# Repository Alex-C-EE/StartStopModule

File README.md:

# StartStopModule
A repo containing original and custom start stop modules for robo sumo and their firmware. Manufacturing files generated.

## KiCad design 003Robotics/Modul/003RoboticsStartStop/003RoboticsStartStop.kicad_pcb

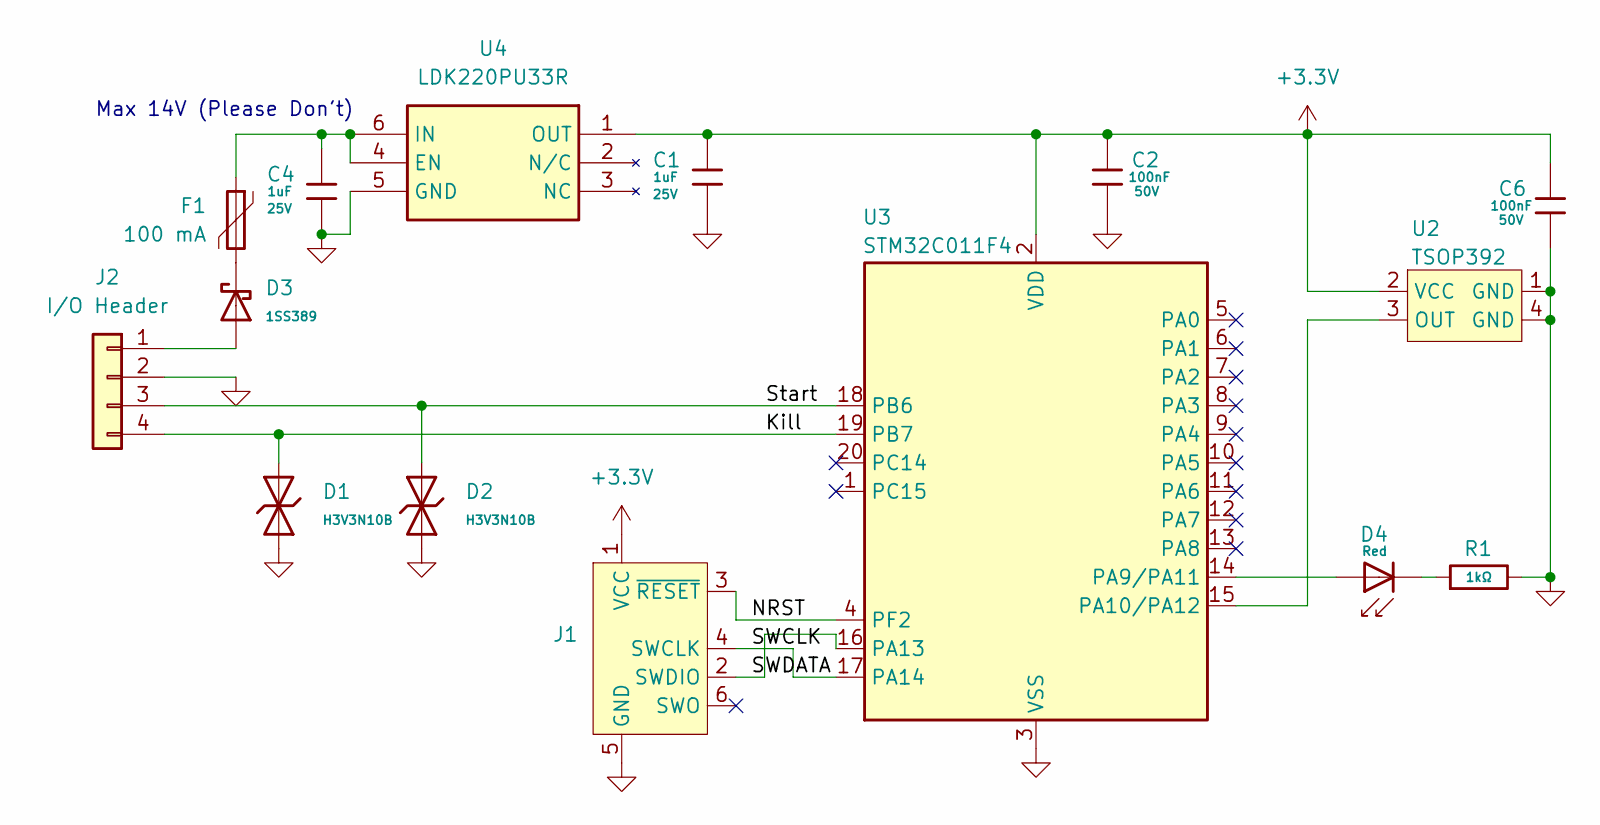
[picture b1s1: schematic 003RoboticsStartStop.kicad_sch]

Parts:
C1, C4: 1uF; C_0402; Voltage Rated 25V; Tolerance ±10%; Part CL05A105KA5NQNC; LCSC C52923
C2, C6: 100nF; C_0402; Voltage Rated 50V; Tolerance ±10%; Part CL05B104KB54PNC; LCSC C307331
D1, D2: H3V3N10B; D_DFN1006-2L; Part H3V3N10B; LCSC C20617909
D3: 1SS389; D_SOD-523; Part 1SS389; LCSC C22466369
D4: Red; D_0603; Part KT-0603R; LCSC C2286
F1: 100 mA; Fuse_0603_1608Metric
J1: Conn_ARM_SWD_TagConnect_TC2030-NL; Tag-Connect_TC2030-IDC-NL_2x03_P1.27mm_Vertical
J2: I/O Header; PinHeader_1x04_P2.54mm_Vertical
R1: 1kΩ; R_0402; Overload Voltage (Max) 50V; Tolerance ±1%; Part 0402WGF1001TCE; LCSC C11702
U2: TSOP392; TVCastSMD4
U3: STM32C011F4; ST_UFQFPN-20_3x3mm_P0.5mm
U4: LDK220PU33R; Mouser Part Number 511-LDK220PU33R

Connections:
+3.3V: C1.1, C2.1, C6.1, J1.1 (VCC), U2.2 (VCC), U3.2 (VDD), U4.1 (OUT)
/Kill: D1.2, J2.4, U3.19 (PB7)
/NRST: J1.3 (~RESET), U3.4 (PF2)
/SWCLK: J1.4 (SWCLK), U3.17 (PA14)
/SWDATA: J1.2 (SWDIO), U3.16 (PA13)
/Start: D2.2, J2.3, U3.18 (PB6)
GND: C1.2, C2.2, C4.2, C6.2, D1.1, D2.1, J1.5 (GND), J2.2, R1.2, U2.1 (GND), U2.4 (GND), U3.3 (VSS), U4.5 (GND)
unnamed: D3.1, F1.2
unnamed: D4.1, R1.1
unnamed: D3.2, J2.1
unnamed: U2.3 (OUT), U3.15 (PA10/PA12)
unnamed: D4.2, U3.14 (PA9/PA11)
unnamed: C4.1, F1.1, U4.4 (EN), U4.6 (IN)

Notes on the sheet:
Max 14V (Please Don't)

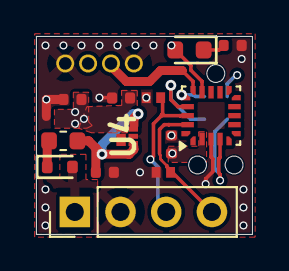
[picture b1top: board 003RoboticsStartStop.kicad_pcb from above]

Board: 4 copper layers, 12.0 x 11.0 mm, 15 parts (1 on the bottom side), 13 nets.

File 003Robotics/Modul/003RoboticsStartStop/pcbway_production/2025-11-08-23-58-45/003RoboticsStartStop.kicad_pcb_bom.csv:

Designator,Quantity,Value,Footprint,Package,MPN,DNP,Mount_Type,Description,LCSC,Stock,Price,Process,Minimum Qty,Attrition Qty,Class,Category,Manufacturer,Part,Voltage Rated,Tolerance,Capacitance,Temperature Coefficient,Resistance,Power(Watts),Type,Overload Voltage (Max),Operating Temperature Range,Height,Mouser Part Number,Mouser Price/Stock,Manufacturer_Name
"C1, C4",2,1uF,C_0402,,,,smt,25V 1uF X5R ±10% 0402 Multilayer Ceramic Capacitors MLCC - SMD/SMT ROHS,C52923,7796525,0.006USD,SMT,20,10,Basic Component,"Capacitors,Multilayer Ceramic Capacitors MLCC - SMD/SMT",Samsung Electro-Mechanics,CL05A105KA5NQNC,25V,±10%,1uF,X5R,,,,,,,,,
"C2, C6",2,100nF,C_0402,,,,smt,50V 100nF X7R ±10% 0402 Multilayer Ceramic Capacitors MLCC - SMD/SMT ROHS,C307331,4519544,0.008USD,SMT,20,10,Basic Component,"Capacitors,Multilayer Ceramic Capacitors MLCC - SMD/SMT",Samsung Electro-Mechanics,CL05B104KB54PNC,50V,±10%,100nF,X7R,,,,,,,,,
"D1, D2",2,H3V3N10B,D_DFN1006-2L,,,,smt,8A 10V 80W 6V Bidirectional 3.3V DFN1006-2L ESD and Surge Protection (TVS/ESD) ROHS,C20617909,5860,0.016USD,SMT,20,10,Preferred Component,"TVS/Fuse/Board Level Protection,Electrostatic And Surge Protection (TVS/ESD)",hongjiacheng,H3V3N10B,,,,,,,,,,,,,
D3,1,1SS389,D_SOD-523,,,,smt,10V Independent Type 500mV@100mA 100mA SOD-523 Schottky Diodes ROHS,C22466369,4454,0.016USD,SMT,20,6,Preferred Component,"Diodes,Schottky Diodes",hongjiacheng,1SS389,,,,,,,,,,,,,
D4,1,Red,D_0603,,,,smt,-40°C~+85°C Red 0603 LED Indication - Discrete ROHS,C2286,2875790,0.009USD,SMT,20,6,Basic Component,"Optocouplers & LEDs & Infrared,Light Emitting Diodes (LED)",Hubei KENTO Elec,KT-0603R,,,,,,,,,,,,,
F1,1,100 mA,Fuse_0603_1608Metric,,,,smt,"Resettable fuse, polymeric positive temperature coefficient",,,,,,,,,,,,,,,,,,,,,,,
J2,1,I/O Header,PinHeader_1x04_P2.54mm_Vertical,,,,tht,"Generic connector, single row, 01x04, script generated (kicad-library-utils/schlib/autogen/connector/)",,,,,,,,,,,,,,,,,,,,,,,
R1,1,1kΩ,R_0402,,,,tht,62.5mW Thick Film Resistors 50V ±100ppm/°C ±1% 1kΩ 0402 Chip Resistor - Surface Mount ROHS,C11702,6792566,0.004USD,SMT,20,10,Basic Component,"Resistors,Chip Resistor - Surface Mount",UNI-ROYAL(Uniroyal Elec),0402WGF1001TCE,,±1%,,±100ppm/°C,1kΩ,62.5mW,Thick Film Resistors,50V,-55°C~+155°C,,,,
U2,1,TSOP392,TVCastSMD4,,,,smt,,,,,,,,,,,,,,,,,,,,,,,,
U3,1,STM32C011F4,ST_UFQFPN-20_3x3mm_P0.5mm,,,,smt,"STMicroelectronics Arm Cortex-M0+ MCU, 16KB flash, 6KB RAM, 48 MHz, 2.0-3.6V, 18 GPIO, UFQFPN20",,,,,,,,,,,,,,,,,,,,,,,
U4,1,LDK220PU33R,LDK220PU33R,,LDK220PU33R,,smt,LDO Voltage Regulators 200 mA low quiescent current and low noise LDO,,,,,,,,,,,,,,,,,,,,0.5,511-LDK220PU33R,https://www.mouser.co.uk/ProductDetail/STMicroelectronics/LD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,STMicroelectronics

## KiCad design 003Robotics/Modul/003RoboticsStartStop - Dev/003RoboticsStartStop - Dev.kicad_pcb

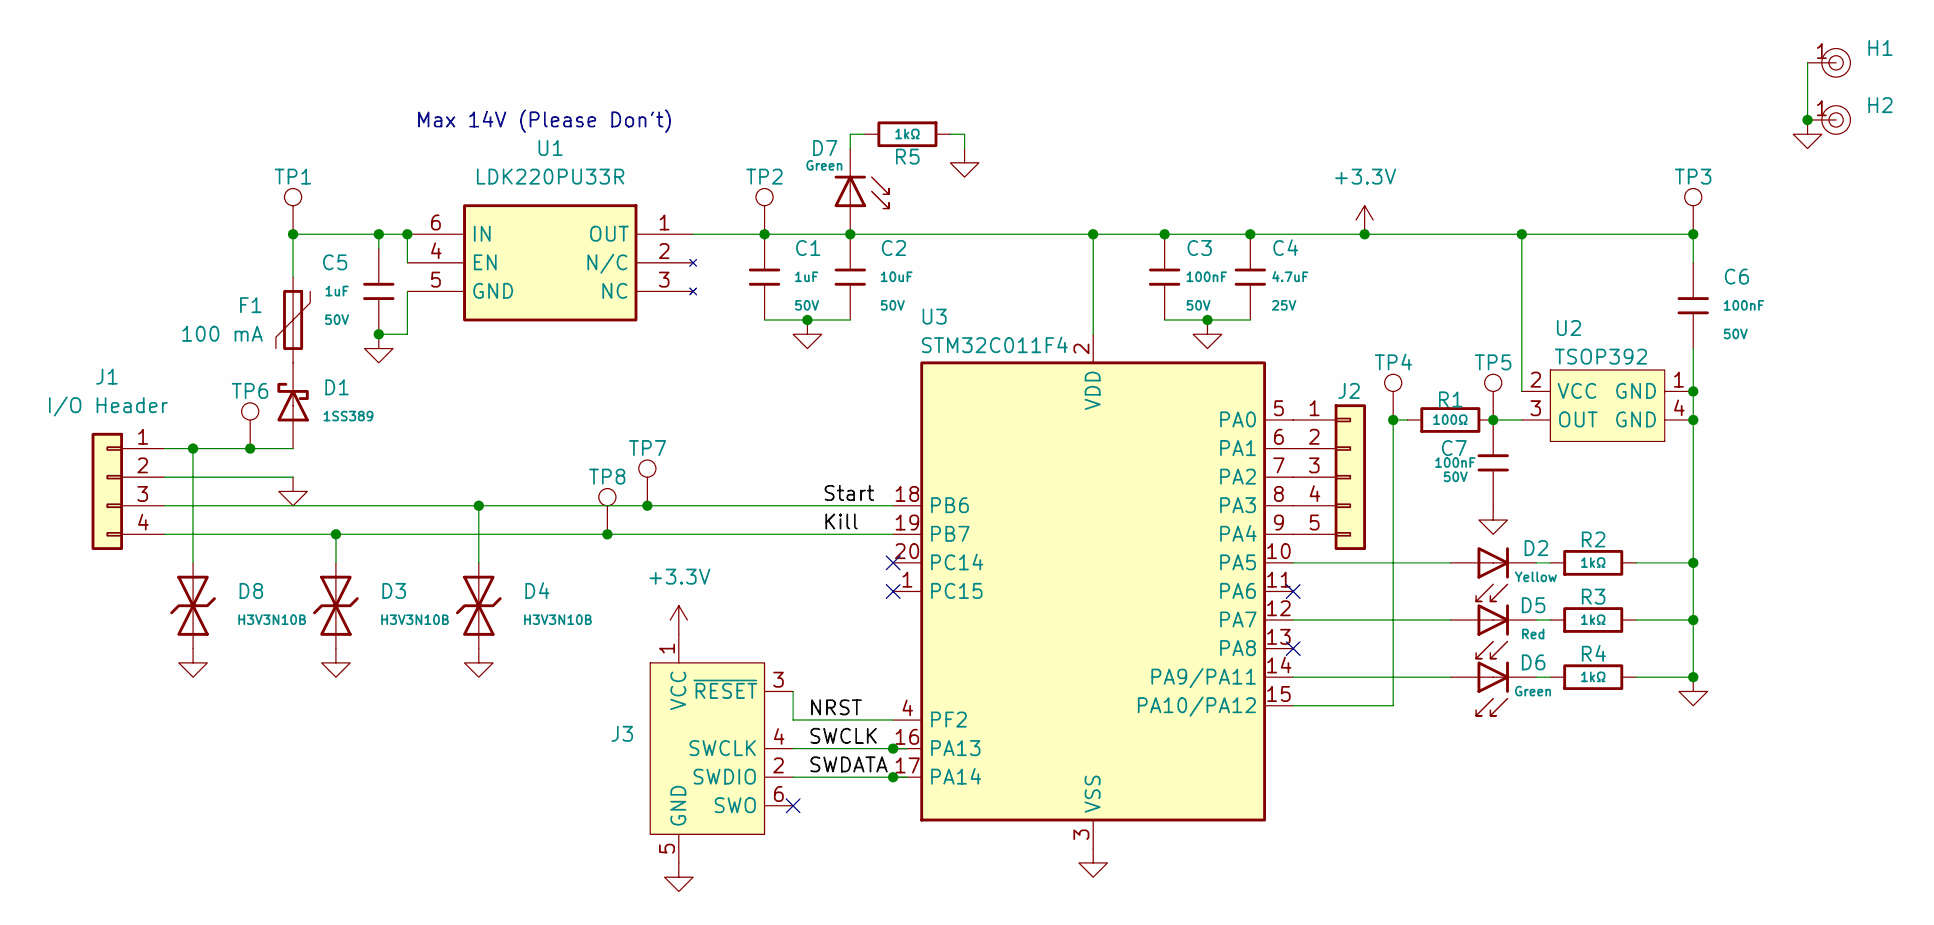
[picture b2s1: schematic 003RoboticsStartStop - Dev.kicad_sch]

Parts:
C1, C5: 1uF; C_0805; Voltage Rated 50V; Tolerance ±10%; Part CL21B105KBFNNNE; LCSC C28323
C2: 10uF; C_0805; Voltage Rated 50V; Tolerance ±10%; Part GRM21BR61H106KE43L; LCSC C440198
C3, C6, C7: 100nF; C_0805; Voltage Rated 50V; Tolerance ±10%; Part CC0805KRX7R9BB104; LCSC C49678
C4: 4.7uF; C_0805; Voltage Rated 25V; Tolerance ±10%; Part CL21A475KAQNNNE; LCSC C1779
D1: 1SS389; D_SOD-523; Part 1SS389; LCSC C22466369
D2: Yellow; D_0805; Part KT-0805Y; LCSC C2296
D3, D4, D8: H3V3N10B; D_DFN1006-2L; Part H3V3N10B; LCSC C20617909
D5: Red; D_0805; Forward Voltage (VF) 1.6V~2.6V; Part NCD0805R1; LCSC C84256
D6, D7: Green; D_0805; Part KT-0805G; LCSC C2297
F1: 100 mA; Fuse_0603_1608Metric
H1, H2: Hole, 3mm
J1: I/O Header; PinHeader_1x04_P2.54mm_Vertical
J2: Conn_01x05; PinHeader_1x05_P2.54mm_Vertical
J3: Conn_ARM_SWD_TagConnect_TC2030-NL; Tag-Connect_TC2030-IDC-NL_2x03_P1.27mm_Vertical
R1: 100Ω; R_0805; Overload Voltage (Max) 150V; Tolerance ±1%; Part 0805W8F1000T5E; LCSC C17408
R2, R3, R4, R5: 1kΩ; R_0805; Overload Voltage (Max) 150V; Tolerance ±1%; Part 0805W8F1001T5E; LCSC C17513
TP1, TP2, TP3, TP4, TP5, TP6, TP7, TP8: TestPoint; PinHeader_1x01_P1.27mm_Vertical
U1: LDK220PU33R; Mouser Part Number 511-LDK220PU33R
U2: TSOP392; TVCastSMD4
U3: STM32C011F4; ST_UFQFPN-20_3x3mm_P0.5mm

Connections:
+3.3V: C1.1, C2.1, C3.1, C4.1, C6.1, D7.2, J3.1 (VCC), TP2.1, TP3.1, U1.1 (OUT), U2.2 (VCC), U3.2 (VDD)
/Kill: D3.2, J1.4, TP8.1, U3.19 (PB7)
/NRST: J3.3 (~RESET), U3.4 (PF2)
/SWCLK: J3.4 (SWCLK), U3.16 (PA13)
/SWDATA: J3.2 (SWDIO), U3.17 (PA14)
/Start: D4.2, J1.3, TP7.1, U3.18 (PB6)
GND: C1.2, C2.2, C3.2, C4.2, C5.2, C6.2, C7.2, D3.1, D4.1, D8.1, H1.1, H2.1, J1.2, J3.5 (GND), R2.2, R3.2, R4.2, R5.1, U1.5 (GND), U2.1 (GND), U2.4 (GND), U3.3 (VSS)
unnamed: D1.1, F1.2
unnamed: D2.1, R2.1
unnamed: D5.1, R3.1
unnamed: D6.1, R4.1
unnamed: D7.1, R5.2
unnamed: D1.2, D8.2, J1.1, TP6.1
unnamed: J2.1, U3.5 (PA0)
unnamed: J2.2, U3.6 (PA1)
unnamed: J2.3, U3.7 (PA2)
unnamed: J2.4, U3.8 (PA3)
unnamed: J2.5, U3.9 (PA4)
unnamed: C5.1, F1.1, TP1.1, U1.4 (EN), U1.6 (IN)
unnamed: C7.1, R1.2, TP5.1, U2.3 (OUT)
unnamed: D2.2, U3.10 (PA5)
unnamed: D5.2, U3.12 (PA7)
unnamed: D6.2, U3.14 (PA9/PA11)
unnamed: R1.1, TP4.1, U3.15 (PA10/PA12)

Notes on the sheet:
Max 14V (Please Don't)

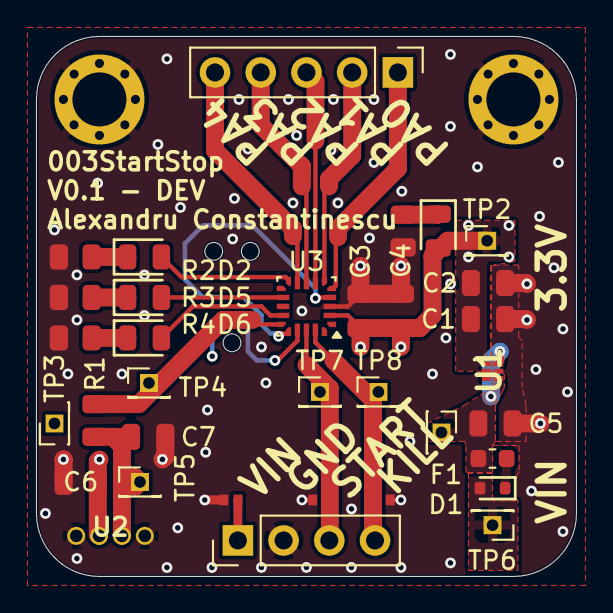
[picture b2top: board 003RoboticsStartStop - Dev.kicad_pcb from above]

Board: 4 copper layers, 30.0 x 30.0 mm, 37 parts (1 on the bottom side), 24 nets.

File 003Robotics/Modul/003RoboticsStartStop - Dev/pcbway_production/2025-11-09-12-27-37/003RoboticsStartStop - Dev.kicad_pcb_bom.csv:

Designator,Quantity,Value,Footprint,Package,MPN,DNP,Mount_Type,Description,LCSC,Stock,Price,Process,Minimum Qty,Attrition Qty,Class,Category,Manufacturer,Part,Voltage Rated,Tolerance,Capacitance,Temperature Coefficient,Operating Temperature,Viewing Angle,Forward Current,Forward Voltage (VF),Luminous Intensity,Dominant Wavelength,Power Dissipation,Emitted Color,Diode Configuration,Lens Color,Resistance,Power(Watts),Type,Overload Voltage (Max),Operating Temperature Range,Height,Mouser Part Number,Mouser Price/Stock,Manufacturer_Name
"C1, C5",2,1uF,C_0805,,,,smt,50V 1uF X7R ±10% 0805 Multilayer Ceramic Capacitors MLCC - SMD/SMT ROHS,C28323,5842208,0.012USD,SMT,20,6,Basic Component,"Capacitors,Multilayer Ceramic Capacitors MLCC - SMD/SMT",Samsung Electro-Mechanics,CL21B105KBFNNNE,50V,±10%,1uF,X7R,,,,,,,,,,,,,,,,,,,
C2,1,10uF,C_0805,,,,smt,50V 10uF X5R ±10% 0805 Multilayer Ceramic Capacitors MLCC - SMD/SMT ROHS,C440198,1026839,0.069USD,SMT,5,4,Basic Component,"Capacitors,Multilayer Ceramic Capacitors MLCC - SMD/SMT",Murata Electronics,GRM21BR61H106KE43L,50V,±10%,10uF,X5R,,,,,,,,,,,,,,,,,,,
"C3, C6, C7",3,100nF,C_0805,,,,smt,50V 100nF X7R ±10% 0805 Multilayer Ceramic Capacitors MLCC - SMD/SMT ROHS,C49678,9212465,0.008USD,SMT,20,10,Basic Component,"Capacitors,Multilayer Ceramic Capacitors MLCC - SMD/SMT",YAGEO,CC0805KRX7R9BB104,50V,±10%,100nF,X7R,,,,,,,,,,,,,,,,,,,
C4,1,4.7uF,C_0805,,,,smt,25V 4.7uF X5R ±10% 0805 Multilayer Ceramic Capacitors MLCC - SMD/SMT ROHS,C1779,817638,0.014USD,SMT,20,10,Basic Component,"Capacitors,Multilayer Ceramic Capacitors MLCC - SMD/SMT",Samsung Electro-Mechanics,CL21A475KAQNNNE,25V,±10%,4.7uF,X5R,,,,,,,,,,,,,,,,,,,
D1,1,1SS389,D_SOD-523,,,,smt,10V Independent Type 500mV@100mA 100mA SOD-523 Schottky Diodes ROHS,C22466369,4454,0.016USD,SMT,20,6,Preferred Component,"Diodes,Schottky Diodes",hongjiacheng,1SS389,,,,,,,,,,,,,,,,,,,,,,,
D2,1,Yellow,D_0805,,,,smt,Yellow 0805 LED Indication - Discrete ROHS,C2296,311326,0.016USD,SMT,20,6,Basic Component,"Optocouplers & LEDs & Infrared,Light Emitting Diodes (LED)",Hubei KENTO Elec,KT-0805Y,,,,,,,,,,,,,,,,,,,,,,,
"D3, D4, D8",3,H3V3N10B,D_DFN1006-2L,,,,smt,8A 10V 80W 6V Bidirectional 3.3V DFN1006-2L ESD and Surge Protection (TVS/ESD) ROHS,C20617909,5860,0.016USD,SMT,20,10,Preferred Component,"TVS/Fuse/Board Level Protection,Electrostatic And Surge Protection (TVS/ESD)",hongjiacheng,H3V3N10B,,,,,,,,,,,,,,,,,,,,,,,
D5,1,Red,D_0805,,,,smt,25mA Colorless transparent lens 67mcd~195mcd -30°C~+85°C 615nm~630nm Individual diode Red 130° 65mW 1.6V~2.6V 0805 LED Indication - Discrete ROHS,C84256,3045161,0.016USD,SMT,20,6,Basic Component,"Optoelectronics,Light Emitting Diodes (LED)",Foshan NationStar Optoelectronics,NCD0805R1,,,,,-30°C~+85°C,130°,25mA,1.6V~2.6V,67mcd~195mcd,615nm~630nm,65mW,Red,Independent Diode,Colorless Transparent Lens,,,,,,,,,
"D6, D7",2,Green,D_0805,,,,smt,Emerald 0805 LED Indication - Discrete ROHS,C2297,769221,0.014USD,SMT,20,6,Basic Component,"Optoelectronics,Light Emitting Diodes (LED)",Hubei KENTO Elec,KT-0805G,,,,,,,,,,,,Emerald,,,,,,,,,,,
F1,1,100 mA,Fuse_0603_1608Metric,,,,smt,"Resettable fuse, polymeric positive temperature coefficient",,,,,,,,,,,,,,,,,,,,,,,,,,,,,,,,,
"H1, H2",2,~,"Hole, 3mm",,,,tht,,,,,,,,,,,,,,,,,,,,,,,,,,,,,,,,,,
J1,1,I/O Header,PinHeader_1x04_P2.54mm_Vertical,,,,tht,"Generic connector, single row, 01x04, script generated (kicad-library-utils/schlib/autogen/connector/)",,,,,,,,,,,,,,,,,,,,,,,,,,,,,,,,,
J2,1,Conn_01x05,PinHeader_1x05_P2.54mm_Vertical,,,,tht,"Generic connector, single row, 01x05, script generated (kicad-library-utils/schlib/autogen/connector/)",,,,,,,,,,,,,,,,,,,,,,,,,,,,,,,,,
R1,1,100Ω,R_0805,,,,smt,125mW Thick Film Resistors 150V ±100ppm/°C ±1% 100Ω 0805 Chip Resistor - Surface Mount ROHS,C17408,2800860,0.005USD,SMT,20,10,Basic Component,"Resistors,Chip Resistor - Surface Mount",UNI-ROYAL(Uniroyal Elec),0805W8F1000T5E,,±1%,,±100ppm/°C,,,,,,,,,,,100Ω,125mW,Thick Film Resistors,150V,-55°C~+155°C,,,,
"R2, R3, R4, R5",4,1kΩ,R_0805,,,,smt,125mW Thick Film Resistors 150V ±100ppm/°C ±1% 1kΩ 0805 Chip Resistor - Surface Mount ROHS,C17513,6720192,0.005USD,SMT,20,10,Basic Component,"Resistors,Chip Resistor - Surface Mount",UNI-ROYAL(Uniroyal Elec),0805W8F1001T5E,,±1%,,±100ppm/°C,,,,,,,,,,,1kΩ,125mW,Thick Film Resistors,150V,-55°C~+155°C,,,,
"TP1, TP2, TP3, TP4, TP5, TP6, TP7, TP8",8,TestPoint,PinHeader_1x01_P1.27mm_Vertical,,,,tht,test point,,,,,,,,,,,,,,,,,,,,,,,,,,,,,,,,,
U1,1,LDK220PU33R,LDK220PU33R,,LDK220PU33R,,smt,LDO Voltage Regulators 200 mA low quiescent current and low noise LDO,,,,,,,,,,,,,,,,,,,,,,,,,,,,,,0.5,511-LDK220PU33R,https://www.mouser.co.uk/ProductDetail/STMicroelectronics/LD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,STMicroelectronics
U2,1,TSOP392,TVCastSMD4,,,,smt,,,,,,,,,,,,,,,,,,,,,,,,,,,,,,,,,,
U3,1,STM32C011F4,ST_UFQFPN-20_3x3mm_P0.5mm,,,,smt,"STMicroelectronics Arm Cortex-M0+ MCU, 16KB flash, 6KB RAM, 48 MHz, 2.0-3.6V, 18 GPIO, UFQFPN20",,,,,,,,,,,,,,,,,,,,,,,,,,,,,,,,,

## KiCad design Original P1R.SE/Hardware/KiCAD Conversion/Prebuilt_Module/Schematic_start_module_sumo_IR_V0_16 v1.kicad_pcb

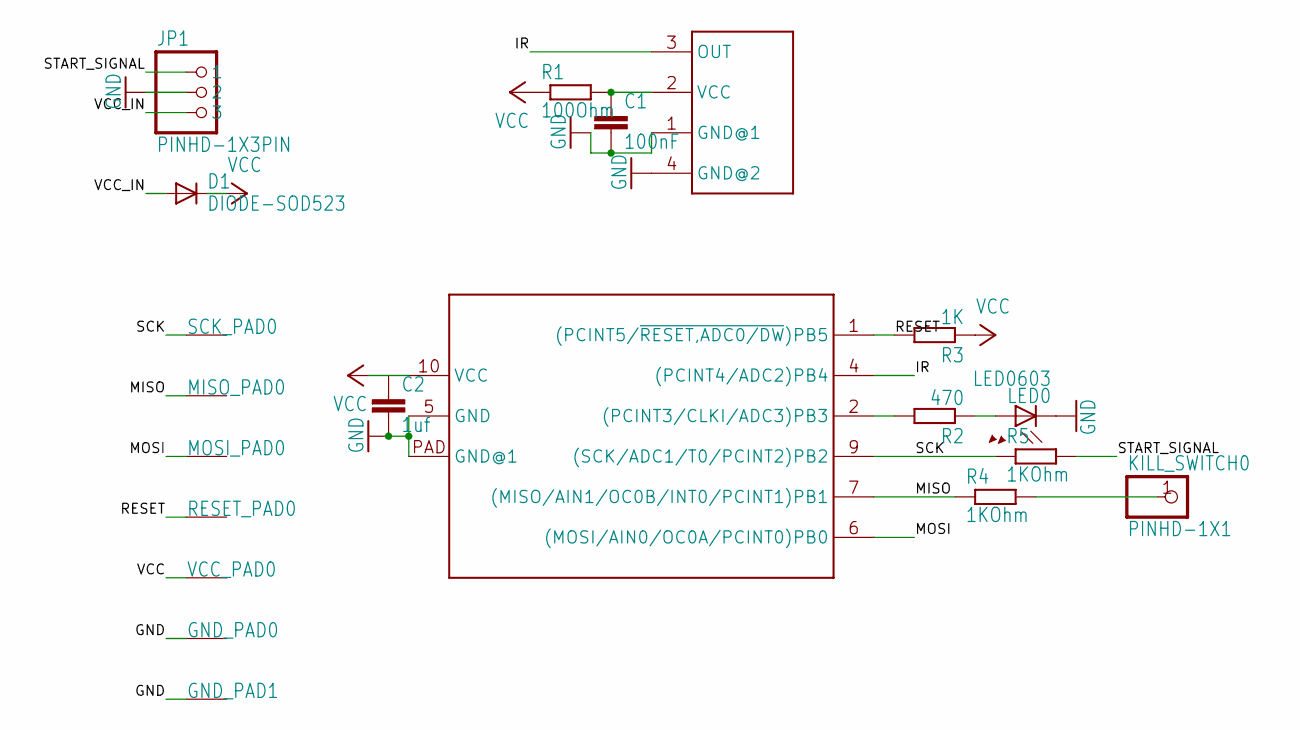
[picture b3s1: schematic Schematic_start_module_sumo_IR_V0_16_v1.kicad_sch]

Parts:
C1: 100nF; C0603
C2: 1uf; C0603
D1: DIODE-SOD523; SOD523
GND_PAD0: PAD50X50; PAD_50X50
GND_PAD1: PAD75X75; PAD_75X75
IR1: TSOP77338TS; TSOP77338
JP1: PINHD-1X3PIN; 1X3
KILL_SWITCH0: PINHD-1X1; 1X01
LED0: LED0603; 0603_SMALL
MISO_PAD0: PAD50X50; PAD_50X50
MOSI_PAD0: mosi; PAD_75X75
R1: 100Ohm; R0603
R2: 470; R0603
R3: 1K; R0603
R4, R5: 1KOhm; R0603
RESET_PAD0: PAD50X50; PAD_50X50
SCK_PAD0: PAD50X50; PAD_50X50
UC0: ATTINY13A; DFN10
VCC_PAD0: PAD50X50; PAD_50X50

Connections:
GND: C1.2, C2.2, GND_PAD0.P$1, GND_PAD1.P$1, IR1.1 (GND@1), IR1.4 (GND@2), JP1.2, LED0.2 (C), UC0.5 (GND), UC0.PAD (GND@1)
IR: IR1.3 (OUT), UC0.4 ((PCINT4/ADC2)PB4)
KILL_SWITCH: KILL_SWITCH0.1, R4.2
MISO: MISO_PAD0.P$1, R4.1, UC0.7 ((MISO/AIN1/OC0B/INT0/PCINT1)PB1)
MOSI: MOSI_PAD0.P$1, UC0.6 ((MOSI/AIN0/OC0A/PCINT0)PB0)
unnamed: R2.2, UC0.2 ((PCINT3/CLKI/ADC3)PB3)
unnamed: LED0.1 (A), R2.1
unnamed: C1.1, IR1.2 (VCC), R1.2
RESET: R3.2, RESET_PAD0.P$1, UC0.1 ((PCINT5/~RESET,ADC0/DW)PB5)
SCK: R5.1, SCK_PAD0.P$1, UC0.9 ((SCK/ADC1/T0/PCINT2)PB2)
START_SIGNAL: JP1.1, R5.2
VCC: C2.1, D1.C, R1.1, R3.1, UC0.10 (VCC), VCC_PAD0.P$1
VCC_IN: D1.A, JP1.3

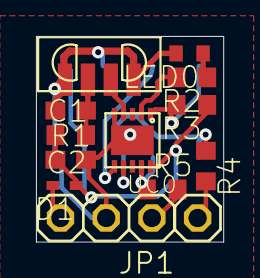
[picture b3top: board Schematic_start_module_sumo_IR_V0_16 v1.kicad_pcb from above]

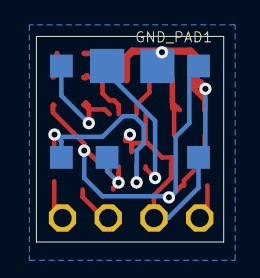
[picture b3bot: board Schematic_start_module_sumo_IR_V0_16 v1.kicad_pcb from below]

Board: 2 copper layers, 10.4 x 11.4 mm, 20 parts (7 on the bottom side), 13 nets.

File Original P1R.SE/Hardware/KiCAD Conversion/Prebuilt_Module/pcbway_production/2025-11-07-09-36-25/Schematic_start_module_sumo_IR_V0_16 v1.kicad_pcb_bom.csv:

Designator,Quantity,Value,Footprint,Package,MPN,DNP,Mount_Type
C1,1,100nF,C0603,,,,tht
C2,1,1uf,C0603,,,,tht
D1,1,,SOD523,,,,tht
"GND_PAD0, MISO_PAD0, RESET_PAD0, SCK_PAD0, VCC_PAD0",5,,PAD_50X50,,,,tht
GND_PAD1,1,,PAD_75X75,,,,tht
IR1,1,TSOP77338TS,TSOP77338,,,,tht
JP1,1,,1X3,,,,tht
KILL_SWITCH0,1,,1X01,,,,tht
LED0,1,,0603_SMALL,,,,tht
MOSI_PAD0,1,mosi,PAD_75X75,,,,tht
R1,1,100Ohm,R0603,,,,tht
R2,1,470,R0603,,,,tht
R3,1,1K,R0603,,,,tht
"R4, R5",2,1KOhm,R0603,,,,tht
UC0,1,ATTINY13A,DFN10,,,,tht

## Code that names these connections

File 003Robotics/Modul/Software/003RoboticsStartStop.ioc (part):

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Mcu.Name=STM32C011F(4-6)Ux
Mcu.Package=UFQFPN20
Mcu.UserName=STM32C011F4Ux
PA11\ [PA9].GPIOParameters=GPIO_Label
PA11\ [PA9].GPIO_Label=OUT_StatusLED
PA11\ [PA9].Signal=GPIO_Output
PA12\ [PA10].GPIOParameters=GPIO_Label,GPIO_ModeDefaultEXTI
PA12\ [PA10].GPIO_Label=IN_IR
PA12\ [PA10].GPIO_ModeDefaultEXTI=GPIO_MODE_IT_FALLING
PA12\ [PA10].Signal=GPXTI12
PA13.Mode=Serial_Wire
PA13.Signal=DEBUG_SWDIO
PA14-BOOT0.Mode=Serial_Wire
PA14-BOOT0.Signal=DEBUG_SWCLK
PB6.GPIOParameters=GPIO_Label
PB6.GPIO_Label=OUT_Start
PB6.Signal=GPIO_Output
PB7.GPIOParameters=GPIO_Label
PB7.GPIO_Label=OUT_Kill
PB7.Signal=GPIO_Output
RCC.HSE_VALUE=8000000
RCC.SYSCLKFreq_VALUE=48000000
board=custom

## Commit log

2025-11-10 Start Good
2025-12-12 Inverted SWDIO/SWCLK to correct pins.
